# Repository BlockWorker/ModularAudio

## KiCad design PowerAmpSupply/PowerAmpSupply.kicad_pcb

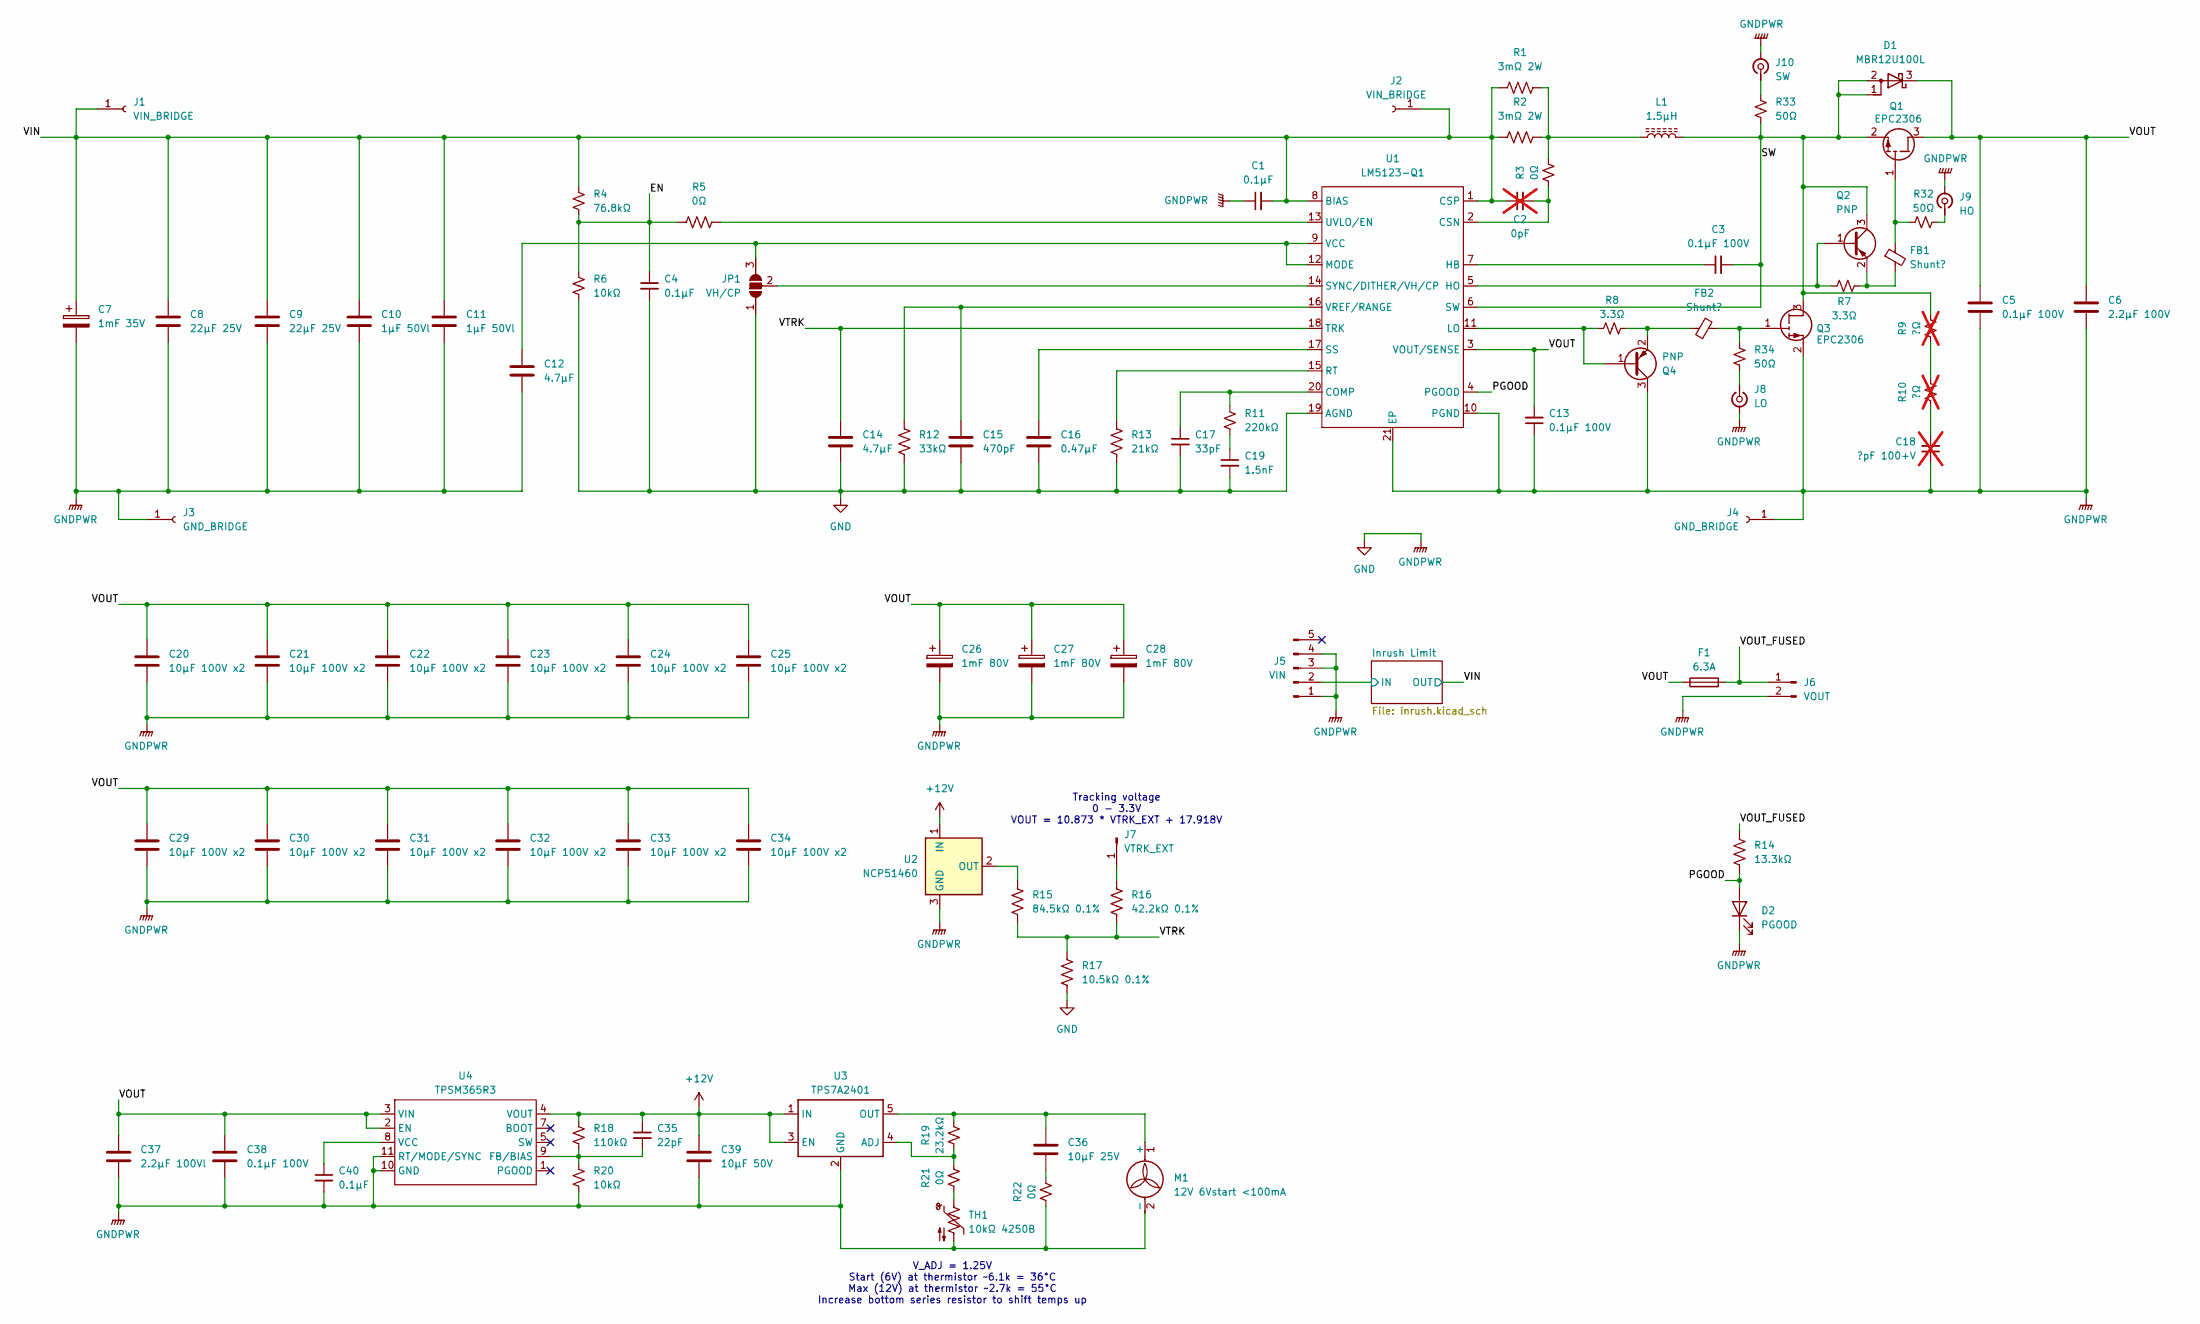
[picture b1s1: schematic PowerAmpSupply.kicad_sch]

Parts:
C1, C4, C40: 0.1µF; C_0603_1608Metric
C2: 0pF; C_0603_1608Metric; not fitted
C3, C5, C13, C38: 0.1µF 100V; C_0603_1608Metric
C6: 2.2µF 100V; C_0805_2012Metric
C7: 1mF 35V; CP_Radial_D10.0mm_P5.00mm
C8, C9: 22µF 25V; C_1210_3225Metric
C10, C11: 1µF 50Vl; C_0805_2012Metric
C12, C14: 4.7µF; C_0603_1608Metric
C15: 470pF; C_0603_1608Metric
C16: 0.47µF; C_0603_1608Metric
C17: 33pF; C_0603_1608Metric
C18: ?pF 100+V; C_0603_1608Metric; not fitted
C19: 1.5nF; C_0603_1608Metric
C20, C21, C22, C23, C24, C25, C29, C30, C31, C32, C33, C34: 10µF 100V x2; C_1210_3225Metric
C26, C27, C28: 1mF 80V; CP_Radial_D16.0mm_P7.50mm
C35: 22pF; C_0603_1608Metric
C36: 10µF 25V; C_0805_2012Metric
C37: 2.2µF 100Vl; C_1206_3216Metric
C39: 10µF 50V; C_1206_3216Metric
D1: MBR12U100L; TO-277B
D2: PGOOD; LED_0805_2012Metric
F1: 6.3A; Fuse_Schurter_MSB
FB1, FB2: Shunt?; L_0402_1005Metric_Pad0.77x0.64mm_HandSolder
J1, J2: VIN_BRIDGE; HolePad_2.5mm_3.5mm
J3, J4: GND_BRIDGE; HolePad_2.5mm_3.5mm
J5: VIN; TE_2042274_Solder
J6: VOUT; TE_644749-2
J7: VTRK_EXT; PinHeader_1x01_P2.54mm_Vertical
J8: LO; TE_CONMHF1-SMD
J9: HO; TE_CONMHF1-SMD
J10: SW; TE_CONMHF1-SMD
JP1: VH/CP; SolderJumper-3_P1.3mm_Open_RoundedPad1.0x1.5mm
L1: 1.5µH; L_Vishay_IHLP-6767
M1: 12V 6Vstart <100mA; Amphenol_MINITEK_0.8_2P_V_BoardEdge
Q1, Q3: EPC2306
Q2, Q4: PNP; HUSON-3-1EP_2x2mm_P1.3mm_EP1.1x1.6mm
R1, R2: 3mΩ 2W; R_0612_1632Metric
R3, R5, R21, R22: 0Ω; R_0603_1608Metric
R4: 76.8kΩ; R_0603_1608Metric
R6, R20: 10kΩ; R_0603_1608Metric
R7, R8: 3.3Ω; R_0603_1608Metric
R9, R10: ?Ω; R_1206_3216Metric; not fitted
R11: 220kΩ; R_0603_1608Metric
R12: 33kΩ; R_0603_1608Metric
R13: 21kΩ; R_0603_1608Metric
R14: 13.3kΩ; R_0603_1608Metric
R15: 84.5kΩ 0.1%; R_0603_1608Metric
R16: 42.2kΩ 0.1%; R_0603_1608Metric
R17: 10.5kΩ 0.1%; R_0603_1608Metric
R18: 110kΩ; R_0603_1608Metric
R19: 23.2kΩ; R_0603_1608Metric
R32, R33, R34: 50Ω; R_0402_1005Metric_Pad0.72x0.64mm_HandSolder
TH1: 10kΩ 4250B; R_0402_1005Metric_Pad0.72x0.64mm_HandSolder
U1: LM5123-Q1; VQFN-20-1EP_3.5x3.5mm_P0.5mm_EP2.05x2.05mm
U2: NCP51460; SOT-23
U3: TPS7A2401; SOT-23-5
U4: TPSM365R3; TI_QFN-FCMOD-HR

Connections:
+12V: C35.1, C39.1, R18.1, U2.1 (IN), U3.1 (IN), U3.3 (EN), U4.4 (VOUT)
/EN: C4.1, R4.2, R5.1, R6.1
/Inrush Limit/IN: J5.2; also elsewhere on the board
/PGOOD: D2.2 (A), R14.2, U1.4 (PGOOD)
/SW: C3.2, D1.1 (A), D1.2 (A), L1.2, Q1.2 (S), Q1.4 (S), Q1.6 (S), Q2.3 (C), Q3.3 (D), Q3.5 (D), Q3.7 (D), R9.2, R33.2, U1.6 (SW)
/VIN: C1.2, C2.1, C7.1, C8.1, C9.1, C10.1, C11.1, J1.1, J2.1, R1.1, R2.1, R4.1, U1.1 (CSP), U1.8 (BIAS); also elsewhere on the board
/VOUT: C5.1, C6.1, C13.2, C20.1, C21.1, C22.1, C23.1, C24.1, C25.1, C26.1, C27.1, C28.1, C29.1, C30.1, C31.1, C32.1, C33.1, C34.1, C37.1, C38.1, D1.3 (K), F1.1, Q1.3 (D), Q1.5 (D), Q1.7 (D), U1.3 (VOUT/SENSE), U4.2 (EN), U4.3 (VIN)
/VOUT_FUSED: F1.2, J6.1, R14.1
/VTRK: C14.1, R15.2, R16.2, R17.1, U1.18 (TRK)
GND: C1.1, C4.2, C5.2, C6.2, C7.2, C8.2, C9.2, C10.2, C11.2, C12.2, C13.1, C14.2, C15.2, C16.2, C17.2, C18.1, C19.2, C20.2, C21.2, C22.2, C23.2, C24.2, C25.2, C26.2, C27.2, C28.2, C29.2, C30.2, C31.2, C32.2, C33.2, C34.2, C37.2, C38.2, C39.2, C40.2, D2.1 (K), J3.1, J4.1, J5.1, J5.3, J5.4, J6.2, J8.2 (Ext), J9.2 (Ext), J10.2 (Ext), JP1.1 (A), M1.2 (-), Q3.2 (S), Q3.4 (S), Q3.6 (S), Q4.3 (C), R6.2, R12.2, R13.2, R17.2, R20.2, R22.2, TH1.2, U1.10 (PGND), U1.19 (AGND), U1.21 (EP), U2.3 (GND), U3.2 (GND), U4.10 (GND), U4.11 (RT/MODE/SYNC); also elsewhere on the board
unnamed: C18.2, R10.1
unnamed: C19.1, R11.2
unnamed: C36.2, R22.1
unnamed: J7.1, R16.1
unnamed: J8.1 (In), R34.2
unnamed: J9.1 (In), R32.2
unnamed: J10.1 (In), R33.1
unnamed: C12.1, JP1.3 (B), U1.9 (VCC), U1.12 (MODE)
unnamed: JP1.2 (C), U1.14 (SYNC/DITHER/VH/CP)
unnamed: L1.1, R1.2, R2.2, R3.2
unnamed: C36.1, M1.1 (+), R19.1, U3.5 (OUT)
unnamed: FB1.1, Q1.1 (G), R32.1
unnamed: Q2.1 (B), R7.1, U1.5 (HO)
unnamed: FB1.2, Q2.2 (E), R7.2
unnamed: FB2.2, Q3.1 (G), R34.1
unnamed: Q4.1 (B), R8.1, U1.11 (LO)
unnamed: FB2.1, Q4.2 (E), R8.2
unnamed: R9.1, R10.2
unnamed: R21.2, TH1.1
unnamed: C17.1, R11.1, U1.20 (COMP)
unnamed: C2.2, R3.1, U1.2 (CSN)
unnamed: C3.1, U1.7 (HB)
unnamed: R13.1, U1.15 (RT)
unnamed: C16.1, U1.17 (SS)
unnamed: R5.2, U1.13 (UVLO/EN)
unnamed: C15.1, R12.1, U1.16 (VREF/RANGE)
unnamed: R15.1, U2.2 (OUT)
unnamed: R19.2, R21.1, U3.4 (ADJ)
unnamed: C35.2, R18.2, R20.1, U4.9 (FB/BIAS)
unnamed: C40.1, U4.8 (VCC)

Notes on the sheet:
V_ADJ = 1.25V Start (6V) at thermistor ~6.1k = 36°C Max (12V) at thermistor ~2.7k = 55°C Increase bottom series resistor to shift temps up
Tracking voltage 0 - 3.3V VOUT = 10.873 * VTRK_EXT + 17.918V

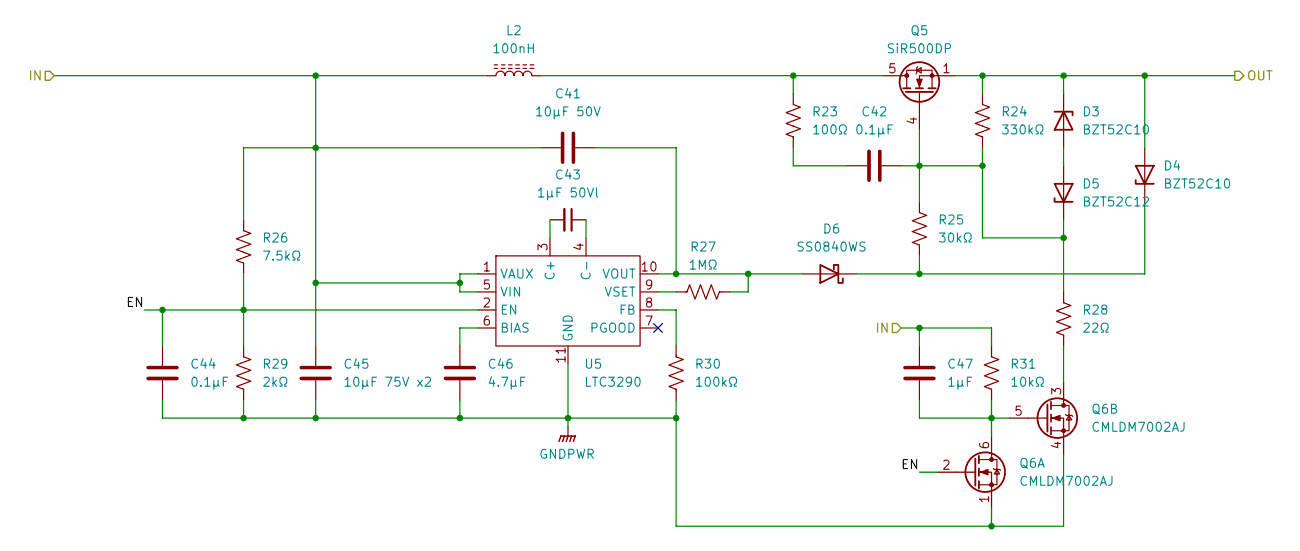
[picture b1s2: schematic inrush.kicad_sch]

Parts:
C41: 10µF 50V; C_1206_3216Metric
C42, C44: 0.1µF; C_0603_1608Metric
C43: 1µF 50Vl; C_0805_2012Metric
C45: 10µF 75V x2; C_1210_3225Metric
C46: 4.7µF; C_0603_1608Metric
C47: 1µF; C_0603_1608Metric
D3, D4: BZT52C10; D_SOD-123
D5: BZT52C12; D_SOD-123
D6: SS0840WS; D_SOD-323_HandSoldering
L2: 100nH; L_Pulse_PG2110HLT
Q5: SiR500DP; PowerPAK_SO-8_Single
Q6: CMLDM7002AJ; SOT-563
R23: 100Ω; R_0603_1608Metric
R24: 330kΩ; R_0603_1608Metric
R25: 30kΩ; R_0603_1608Metric
R26: 7.5kΩ; R_0603_1608Metric
R27: 1MΩ; R_0603_1608Metric
R28: 22Ω; R_0603_1608Metric
R29: 2kΩ; R_0603_1608Metric
R30: 100kΩ; R_0603_1608Metric
R31: 10kΩ; R_0603_1608Metric
U5: LTC3290; MSOP-10-1EP_3x3mm_P0.5mm_EP1.68x1.88mm

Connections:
/Inrush Limit/EN: C44.1, Q6.2 (G), R26.2, R29.1, U5.2 (EN)
/Inrush Limit/IN: C41.1, C45.1, C47.1, L2.1, R26.1, R31.1, U5.1 (VAUX), U5.5 (VIN); also elsewhere on the board
/VIN: D3.1 (K), D4.2 (A), Q5.1 (S), Q5.2 (S), Q5.3 (S), R24.1; also elsewhere on the board
GND: C44.2, C45.2, C46.2, Q6.1 (S), Q6.4 (S), R29.2, R30.2, U5.11 (GND); also elsewhere on the board
unnamed: C42.1, R23.2
unnamed: D3.2 (A), D5.2 (A)
unnamed: D4.1 (K), D6.1 (K), R25.2
unnamed: C42.2, D5.1 (K), Q5.4 (G), R24.2, R25.1, R28.1
unnamed: C41.2, D6.2 (A), R27.2, U5.10 (VOUT)
unnamed: L2.2, Q5.5 (D), R23.1
unnamed: C47.2, Q6.5 (G), Q6.6 (D), R31.2
unnamed: Q6.3 (D), R28.2
unnamed: C46.1, U5.6 (BIAS)
unnamed: C43.2, U5.3 (C+)
unnamed: C43.1, U5.4 (C-)
unnamed: R30.1, U5.8 (FB)
unnamed: R27.1, U5.9 (VSET)

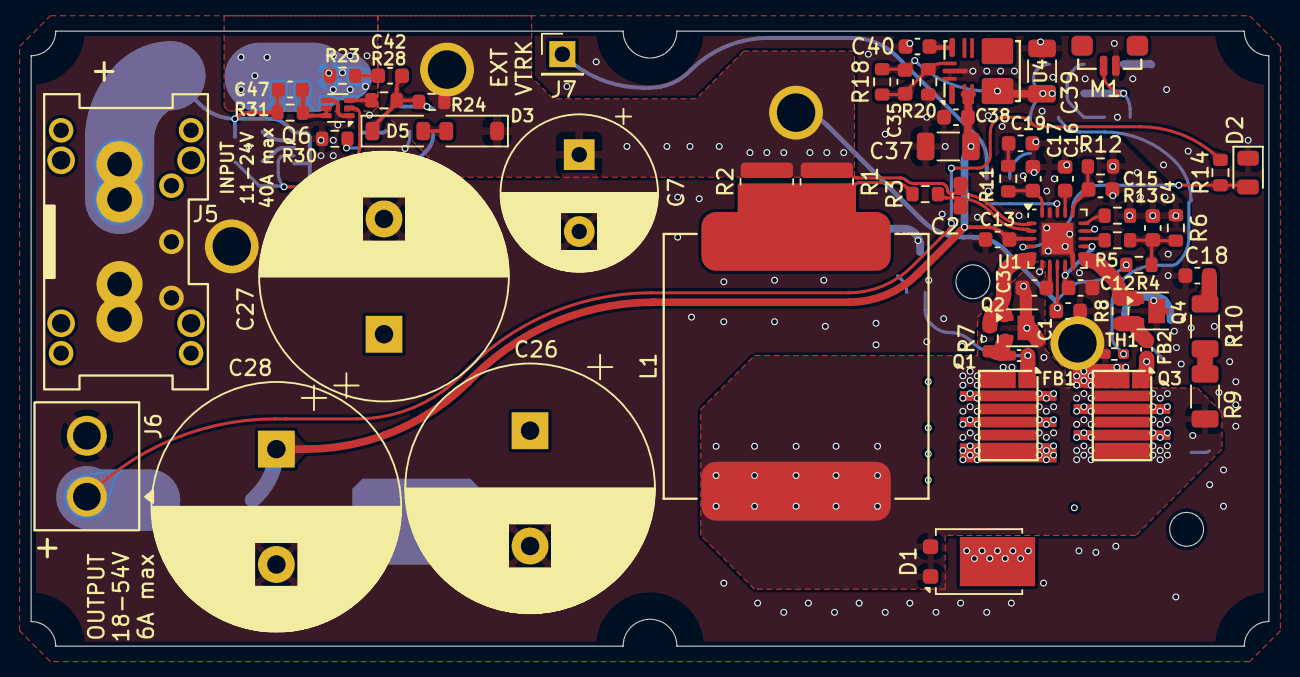
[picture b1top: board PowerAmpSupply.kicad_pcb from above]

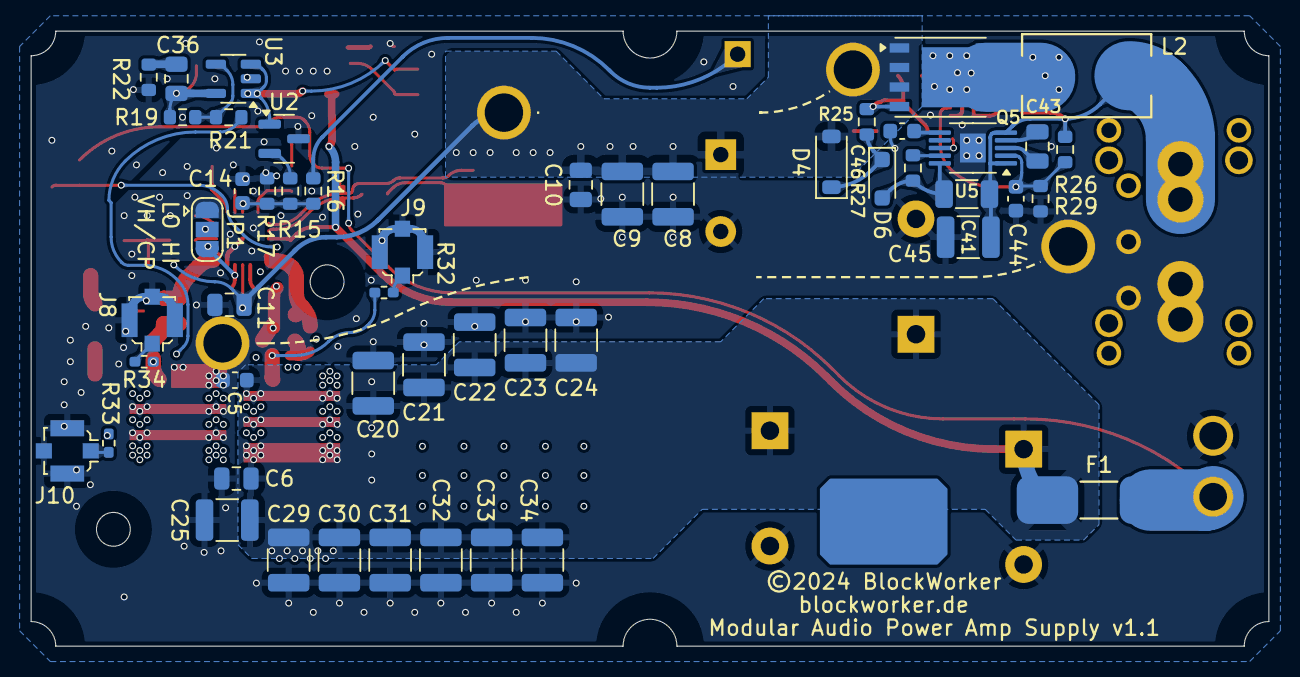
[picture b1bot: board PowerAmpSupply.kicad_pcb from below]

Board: 4 copper layers, 80.5 x 40.0 mm, 118 parts (51 on the bottom side), 54 nets.

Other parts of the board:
HS: ATS-xPX035035035_NoMounts
Logo: BW_Logo_7.5x4.8mm

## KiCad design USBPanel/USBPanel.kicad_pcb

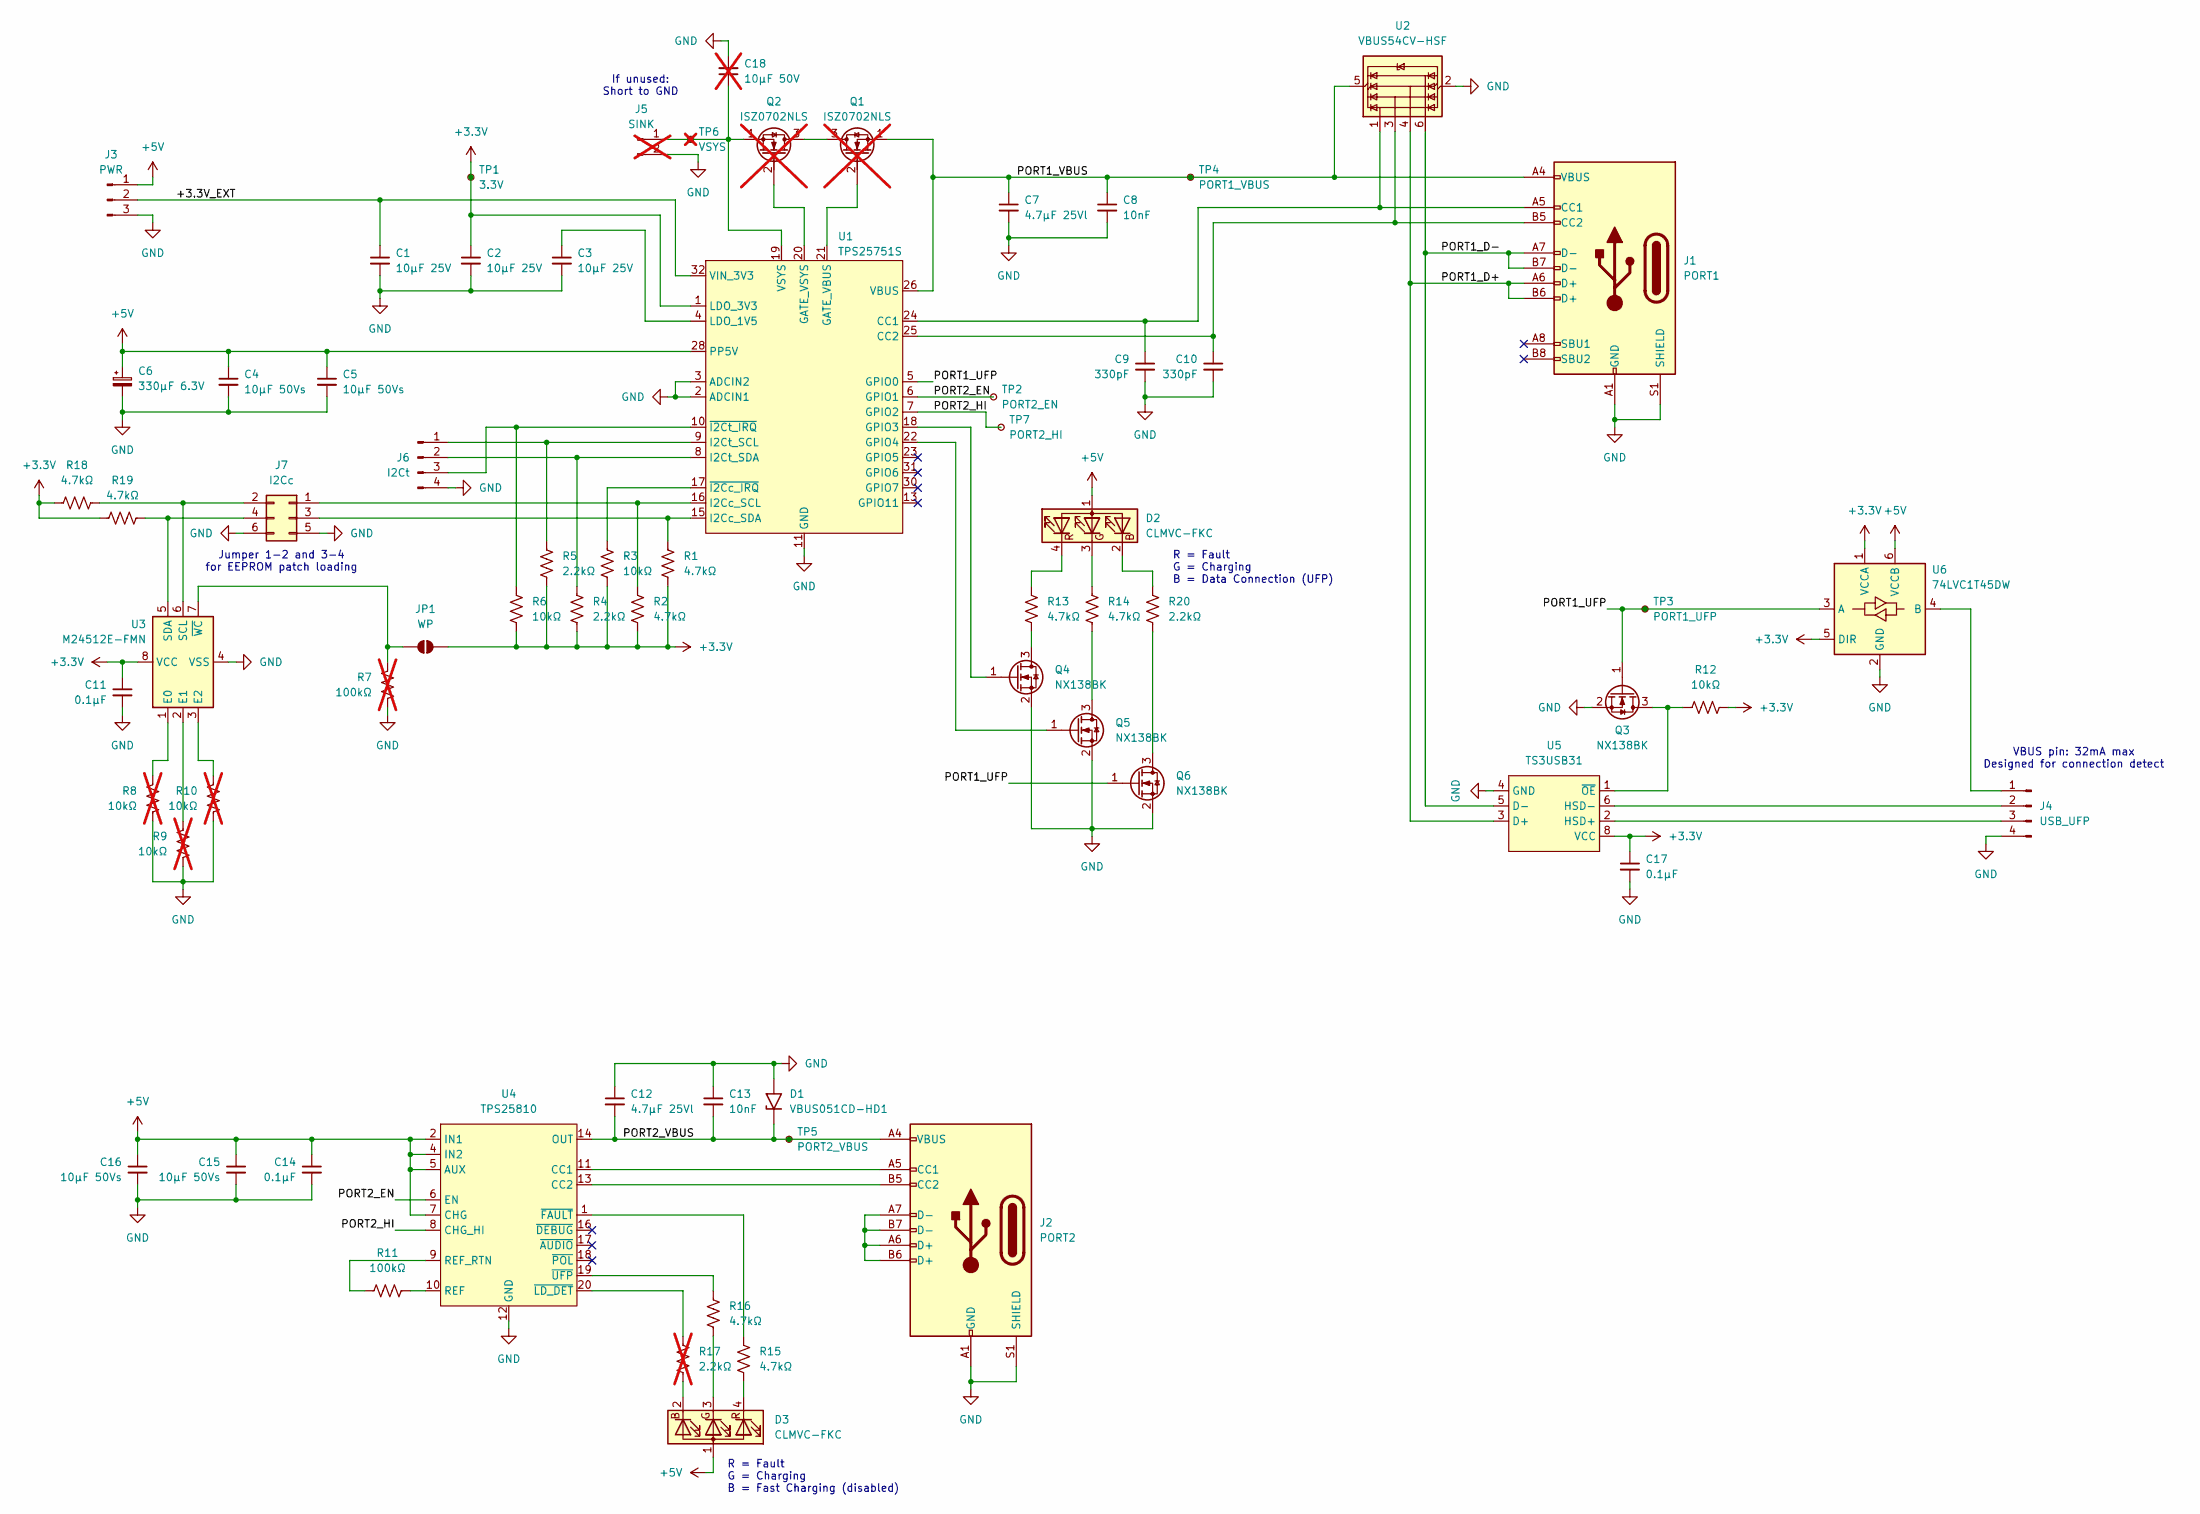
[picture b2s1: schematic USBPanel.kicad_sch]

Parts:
C1, C2, C3: 10μF 25V; C_0805_2012Metric
C4, C5, C15, C16: 10μF 50Vs; C_0805_2012Metric
C6: 330μF 6.3V; CP_Elec_6.3x5.9
C7, C12: 4.7μF 25Vl; C_0805_2012Metric
C8, C13: 10nF; C_0603_1608Metric
C9, C10: 330pF; C_0603_1608Metric
C11, C14, C17: 0.1μF; C_0603_1608Metric
C18: 10μF 50V; C_1206_3216Metric; not fitted
D1: VBUS051CD-HD1; D_0402_1005Metric
D2, D3: CLMVC-FKC; LED_Cree-PLCC4_2x2mm_CW
J1: PORT1; USB_C_Receptacle_Amphenol_12402082E512A
J2: PORT2; USB_C_Receptacle_Amphenol_12402082E512A
J3: PWR; Molex_Nano-Fit_105309-xx03_1x03_P2.50mm_Vertical
J4: USB_UFP; Amphenol_MINITEK_WTB_1.25_4P
J5: SINK; Molex_Nano-Fit_105309-xx02_1x02_P2.50mm_Vertical; not fitted
J6: I2Ct; PinHeader_1x04_P2.54mm_Vertical
J7: I2Cc; PinHeader_2x03_P2.54mm_Vertical
JP1: WP; SolderJumper-2_P1.3mm_Open_RoundedPad1.0x1.5mm
Q1, Q2: ISZ0702NLS; Infineon_PG-TSDSON-8-40; not fitted
Q3, Q4, Q5, Q6: NX138BK; SOT-23
R1, R2, R13, R14, R15, R16, R18, R19: 4.7kΩ; R_0603_1608Metric
R3, R6, R12: 10kΩ; R_0603_1608Metric
R4, R5, R20: 2.2kΩ; R_0603_1608Metric
R7: 100kΩ; R_0603_1608Metric; not fitted
R8, R9, R10: 10kΩ; R_0603_1608Metric; not fitted
R11: 100kΩ; R_0603_1608Metric
R17: 2.2kΩ; R_0603_1608Metric; not fitted
TP1: 3.3V; TP_0603_1608Metric_Fused
TP2: PORT2_EN; TP_0603_1608Metric_Fused
TP3: PORT1_UFP; TP_0603_1608Metric_Fused
TP4: PORT1_VBUS; TP_0603_1608Metric_Fused
TP5: PORT2_VBUS; TP_0603_1608Metric_Fused
TP6: VSYS; TP_0603_1608Metric_Fused; not fitted
TP7: PORT2_HI; TP_0603_1608Metric_Fused
U1: TPS25751S; VQFN-32-1EP_4x4mm_P0.4mm_EP2.8x2.8mm
U2: VBUS54CV-HSF; Vishay_LLP75-6L
U3: M24512E-FMN; SOIC-8_3.9x4.9mm_P1.27mm
U4: TPS25810; Texas_RVC0020A_WQFN-20-1EP_3x4mm_P0.5mm_EP2.6x1.6mm
U5: TS3USB31; Texas_RSE0008A_UQFN-8_1.5x1.5mm_P0.5mm
U6: 74LVC1T45DW; SOT-363_SC-70-6

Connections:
+3.3V: C2.1, C11.1, C17.1, JP1.2 (B), R1.2, R2.2, R3.2, R4.2, R5.2, R6.2, R12.1, R18.1, R19.1, TP1.1, U1.1 (LDO_3V3), U3.8 (VCC), U5.8 (VCC), U6.1 (VCCA), U6.5 (DIR)
+5V: C4.1, C5.1, C6.1, C14.1, C15.1, C16.1, D2.1 (A), D3.1 (A), J3.1, U1.28 (PP5V), U1.29 (PP5V), U4.2 (IN1), U4.3 (IN1), U4.4 (IN2), U4.5 (AUX), U4.7 (CHG), U6.6 (VCCB)
/+3.3V_EXT: C1.1, J3.2, U1.32 (VIN_3V3)
/PORT1_D+: J1.A6 (D+), J1.B6 (D+), U2.4 (I/O3), U5.3 (D+)
/PORT1_D-: J1.A7 (D-), J1.B7 (D-), U2.6 (I/O4), U5.5 (D-)
/PORT1_UFP: Q3.1 (G), Q6.1 (G), TP3.1, U1.5 (GPIO0), U6.3 (A)
/PORT1_VBUS: C7.1, C8.1, J1.A4 (VBUS), J1.A9 (VBUS), J1.B4 (VBUS), J1.B9 (VBUS), Q1.1 (S), TP4.1, U1.26 (VBUS), U1.27 (VBUS), U2.5 (VBUS)
/PORT2_EN: TP2.1, U1.6 (GPIO1), U4.6 (EN)
/PORT2_HI: TP7.1, U1.7 (GPIO2), U4.8 (CHG_HI)
/PORT2_VBUS: C12.2, C13.2, D1.1 (A1), J2.A4 (VBUS), J2.A9 (VBUS), J2.B4 (VBUS), J2.B9 (VBUS), TP5.1, U4.14 (OUT), U4.15 (OUT)
GND: C1.2, C2.2, C3.2, C4.2, C5.2, C6.2, C7.2, C8.2, C9.2, C10.2, C11.2, C12.1, C13.1, C14.2, C15.2, C16.2, C17.2, C18.2, D1.2 (A2), J1.A1 (GND), J1.A12 (GND), J1.B1 (GND), J1.B12 (GND), J1.S1 (SHIELD), J2.A1 (GND), J2.A12 (GND), J2.B1 (GND), J2.B12 (GND), J2.S1 (SHIELD), J3.3, J4.4, J5.2, J6.4, J7.5, J7.6, Q3.2 (S), Q4.2 (S), Q5.2 (S), Q6.2 (S), R7.2, R8.2, R9.2, R10.2, U1.2 (ADCIN1), U1.3 (ADCIN2), U1.11 (GND), U1.12 (GND), U1.14 (GND), U1.33 (GND), U2.2 (GND), U3.4 (VSS), U4.12 (GND), U4.21 (GND), U5.4 (GND), U6.2 (GND)
unnamed: D2.2 (BK), R20.1
unnamed: D2.3 (GK), R14.1
unnamed: D2.4 (RK), R13.1
unnamed: D3.2 (BK), R17.2
unnamed: D3.3 (GK), R16.2
unnamed: D3.4 (RK), R15.2
unnamed: C9.1, J1.A5 (CC1), U1.24 (CC1), U2.1 (I/O1)
unnamed: C10.1, J1.B5 (CC2), U1.25 (CC2), U2.3 (I/O2)
unnamed: J2.A5 (CC1), U4.11 (CC1)
unnamed: J2.B5 (CC2), U4.13 (CC2)
unnamed: J2.A6 (D+), J2.A7 (D-), J2.B6 (D+), J2.B7 (D-)
unnamed: J4.1, U6.4 (B)
unnamed: J4.2, U5.6 (HSD-)
unnamed: J4.3, U5.2 (HSD+)
unnamed: C18.1, J5.1, Q2.1 (S), TP6.1, U1.19 (VSYS)
unnamed: J6.1, R5.1, U1.9 (I2Ct_SCL)
unnamed: J6.2, R4.1, U1.8 (I2Ct_SDA)
unnamed: J6.3, R6.1, U1.10 (~I2Ct_IRQ)
unnamed: J7.1, R2.1, U1.16 (I2Cc_SCL)
unnamed: J7.2, R18.2, U3.6 (SCL)
unnamed: J7.3, R1.1, U1.15 (I2Cc_SDA)
unnamed: J7.4, R19.2, U3.5 (SDA)
unnamed: JP1.1 (A), R7.1, U3.7 (~WC)
unnamed: Q1.3 (D), Q2.3 (D)
unnamed: Q1.2 (G), U1.21 (GATE_VBUS)
unnamed: Q2.2 (G), U1.20 (GATE_VSYS)
unnamed: Q3.3 (D), R12.2, U5.1 (~OE)
unnamed: Q4.3 (D), R13.2
unnamed: Q4.1 (G), U1.18 (GPIO3)
unnamed: Q5.3 (D), R14.2
unnamed: Q5.1 (G), U1.22 (GPIO4)
unnamed: Q6.3 (D), R20.2
unnamed: C3.1, U1.4 (LDO_1V5)
unnamed: R3.1, U1.17 (~I2Cc_IRQ)
unnamed: R8.1, U3.1 (E0)
unnamed: R9.1, U3.2 (E1)
unnamed: R10.1, U3.3 (E2)
unnamed: R11.2, U4.10 (REF)
unnamed: R11.1, U4.9 (REF_RTN)
unnamed: R15.1, U4.1 (~FAULT)
unnamed: R17.1, U4.20 (~LD_DET)
unnamed: R16.1, U4.19 (~UFP)

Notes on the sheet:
Jumper 1-2 and 3-4 for EEPROM patch loading
VBUS pin: 32mA max Designed for connection detect
R = Fault G = Charging B = Fast Charging (disabled)
R = Fault G = Charging B = Data Connection (UFP)
If unused: Short to GND

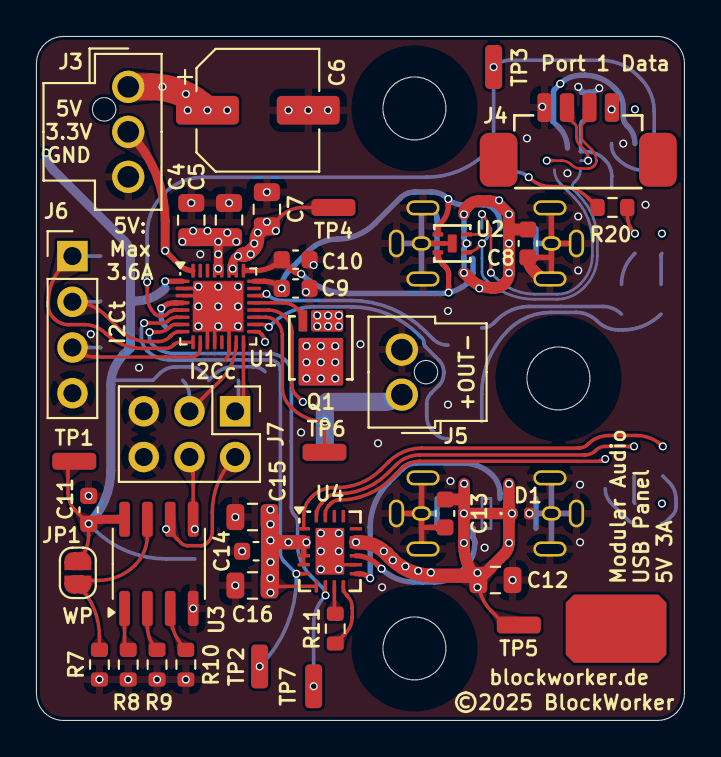
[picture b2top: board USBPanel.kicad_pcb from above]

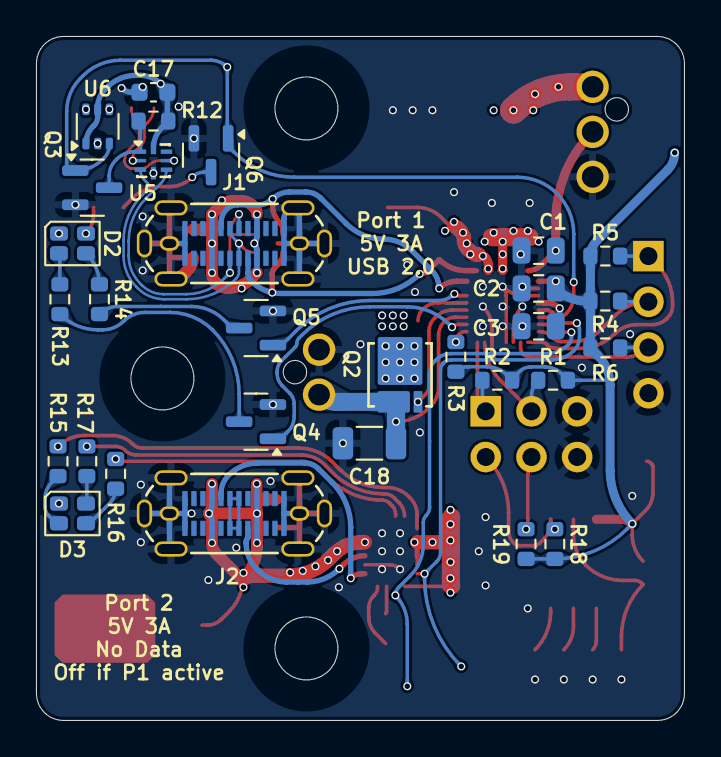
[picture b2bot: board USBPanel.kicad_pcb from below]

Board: 6 copper layers, 36.0 x 38.0 mm, 68 parts (30 on the bottom side), 53 nets.

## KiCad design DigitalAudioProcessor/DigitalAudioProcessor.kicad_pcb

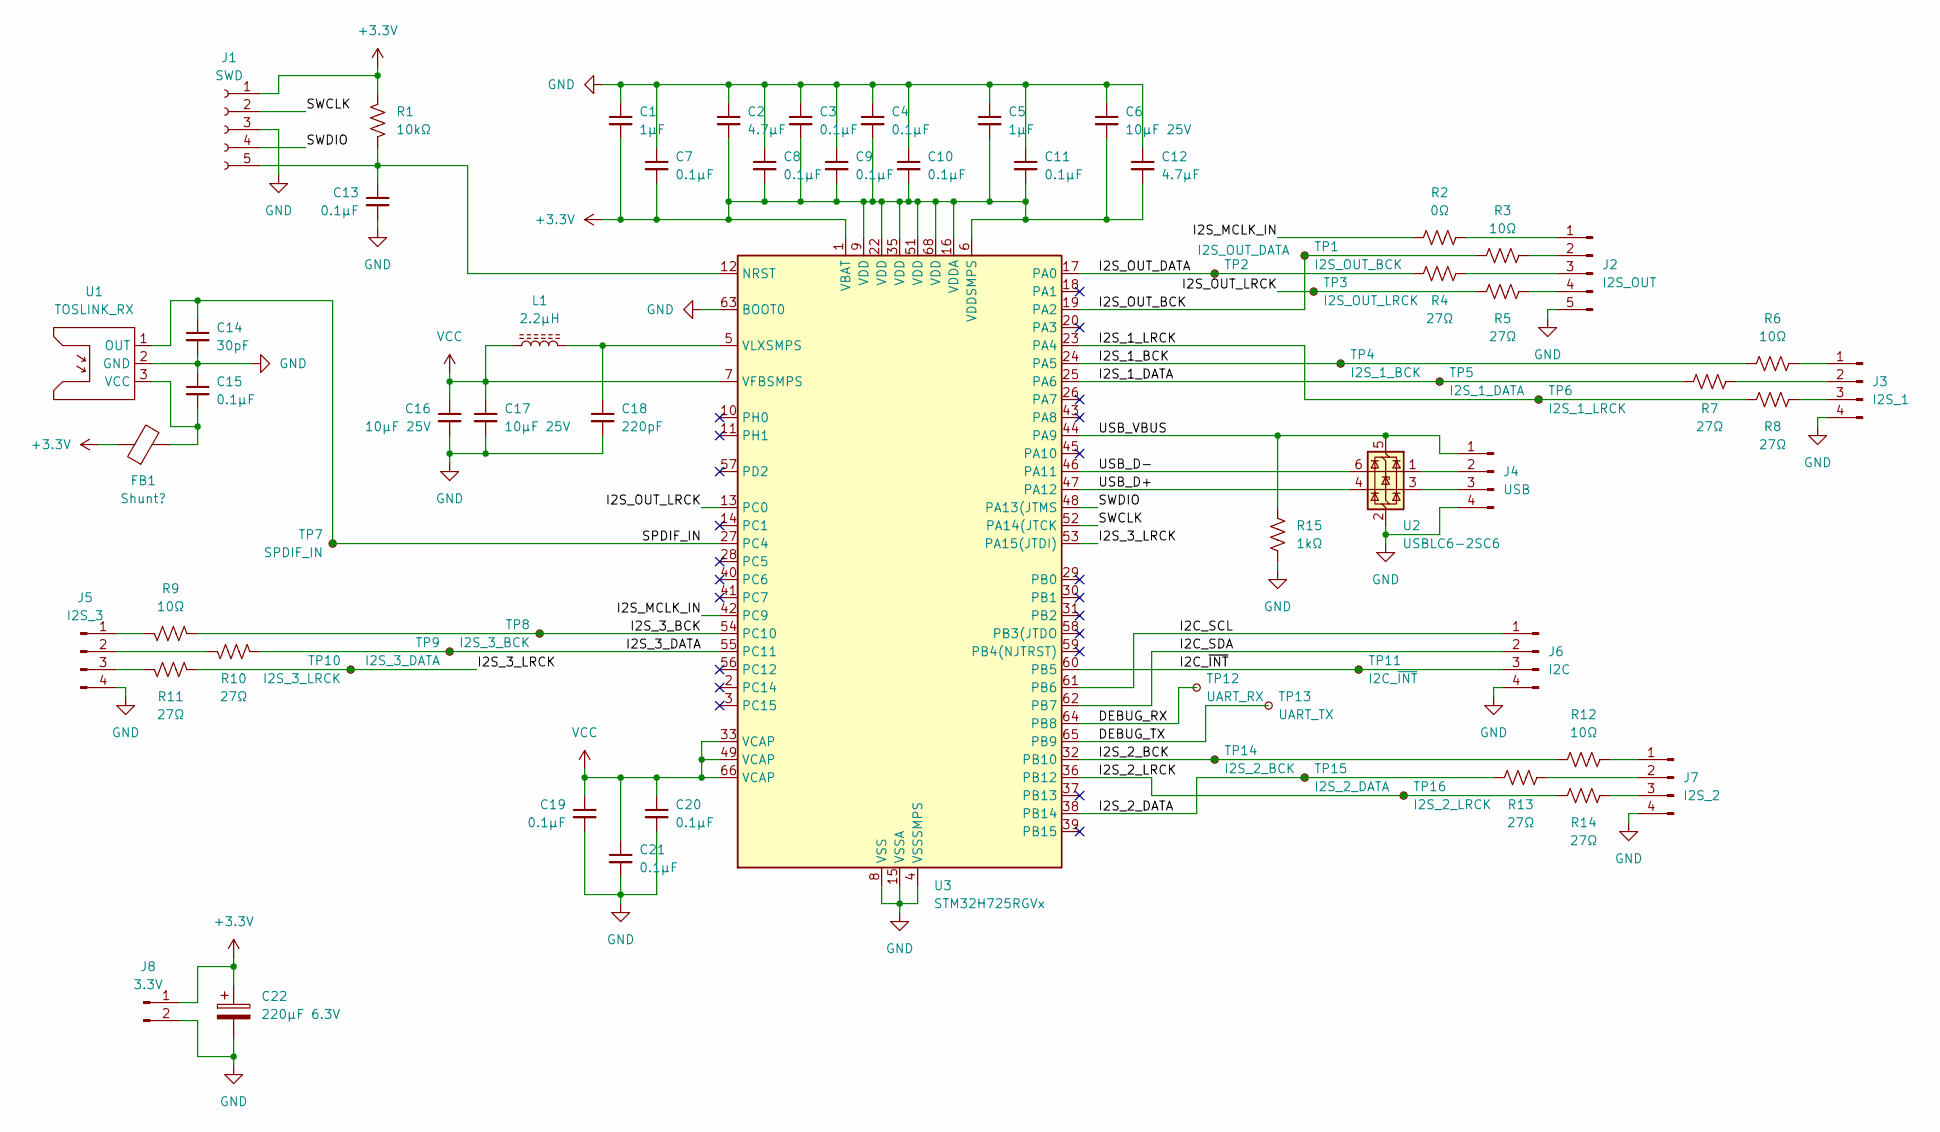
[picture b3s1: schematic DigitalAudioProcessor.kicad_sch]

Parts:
C1, C5: 1µF; C_0603_1608Metric
C2, C12: 4.7µF; C_0603_1608Metric
C3, C4, C7, C8, C9, C10, C11, C13, C15, C19, C20, C21: 0.1µF; C_0603_1608Metric
C6, C16, C17: 10µF 25V; C_0805_2012Metric
C14: 30pF; C_0603_1608Metric
C18: 220pF; C_0603_1608Metric
C22: 220µF 6.3V; CP_Elec_5x5.8
FB1: Shunt?; L_0603_1608Metric
J1: SWD; PinSocket_1x05_P1.27mm_Vertical_SMD_Pin1Right
J2: I2S_OUT; Amphenol_MINITEK_WTB_1.25_5P
J3: I2S_1; Amphenol_MINITEK_WTB_1.25_4P
J4: USB; Amphenol_MINITEK_WTB_1.25_4P
J5: I2S_3; Amphenol_MINITEK_WTB_1.25_4P
J6: I2C; Amphenol_MINITEK_WTB_1.25_4P
J7: I2S_2; Amphenol_MINITEK_WTB_1.25_4P
J8: 3.3V; Amphenol_MINITEK_WTB_1.25_2P
L1: 2.2µH; L_0805_2012Metric
R1: 10kΩ; R_0603_1608Metric
R2: 0Ω; R_0603_1608Metric
R3, R6, R9, R12: 10Ω; R_0603_1608Metric
R4, R5, R7, R8, R10, R11, R13, R14: 27Ω; R_0603_1608Metric
R15: 1kΩ; R_0603_1608Metric
TP1: I2S_OUT_BCK; TP_0603_1608Metric_Fused
TP2: I2S_OUT_DATA; TP_0603_1608Metric_Fused
TP3: I2S_OUT_LRCK; TP_0603_1608Metric_Fused
TP4: I2S_1_BCK; TP_0603_1608Metric_Fused
TP5: I2S_1_DATA; TP_0603_1608Metric_Fused
TP6: I2S_1_LRCK; TP_0603_1608Metric_Fused
TP7: SPDIF_IN; TP_0603_1608Metric_Fused
TP8: I2S_3_BCK; TP_0603_1608Metric_Fused
TP9: I2S_3_DATA; TP_0603_1608Metric_Fused
TP10: I2S_3_LRCK; TP_0603_1608Metric_Fused
TP11: I2C_~{INT}; TP_0603_1608Metric_Fused
TP12: UART_RX; TP_0603_1608Metric_Fused
TP13: UART_TX; TP_0603_1608Metric_Fused
TP14: I2S_2_BCK; TP_0603_1608Metric_Fused
TP15: I2S_2_DATA; TP_0603_1608Metric_Fused
TP16: I2S_2_LRCK; TP_0603_1608Metric_Fused
U1: TOSLINK_RX; DLR2180
U2: USBLC6-2SC6; SOT-23-6
U3: STM32H725RGVx; QFN-68-1EP_8x8mm_P0.4mm_EP6.4x6.4mm

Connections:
+3.3V: C1.2, C2.2, C3.2, C4.2, C5.2, C6.2, C7.2, C8.2, C9.2, C10.2, C11.2, C12.2, C22.1, FB1.1, J1.1, J8.1, R1.1, U3.1 (VBAT), U3.6 (VDDSMPS), U3.9 (VDD), U3.16 (VDDA), U3.22 (VDD), U3.35 (VDD), U3.51 (VDD), U3.68 (VDD)
/DEBUG_RX: TP12.1, U3.64 (PB8)
/DEBUG_TX: TP13.1, U3.65 (PB9)
/I2C_SCL: J6.1, U3.61 (PB6)
/I2C_SDA: J6.2, U3.62 (PB7)
/I2C_~INT: J6.3, TP11.1, U3.60 (PB5)
/I2S_1_BCK: R6.1, TP4.1, U3.24 (PA5)
/I2S_1_DATA: R7.1, TP5.1, U3.25 (PA6)
/I2S_1_LRCK: R8.1, TP6.1, U3.23 (PA4)
/I2S_2_BCK: R12.1, TP14.1, U3.32 (PB10)
/I2S_2_DATA: R13.1, TP15.1, U3.38 (PB14)
/I2S_2_LRCK: R14.1, TP16.1, U3.36 (PB12)
/I2S_3_BCK: R9.1, TP8.1, U3.54 (PC10)
/I2S_3_DATA: R10.1, TP9.1, U3.55 (PC11)
/I2S_3_LRCK: R11.1, TP10.1, U3.53 (PA15(JTDI))
/I2S_MCLK_IN: R2.1, U3.42 (PC9)
/I2S_OUT_BCK: R3.1, TP1.1, U3.19 (PA2)
/I2S_OUT_DATA: R4.1, TP2.1, U3.17 (PA0)
/I2S_OUT_LRCK: R5.1, TP3.1, U3.13 (PC0)
/SPDIF_IN: C14.1, TP7.1, U1.1 (OUT), U3.27 (PC4)
/SWCLK: J1.2, U3.52 (PA14(JTCK)
/SWDIO: J1.4, U3.48 (PA13(JTMS)
/USB_D+: U2.4 (I/O2), U3.47 (PA12)
/USB_D-: U2.6 (I/O1), U3.46 (PA11)
/USB_VBUS: J4.1, R15.2, U2.5 (VBUS), U3.44 (PA9)
GND: C1.1, C2.1, C3.1, C4.1, C5.1, C6.1, C7.1, C8.1, C9.1, C10.1, C11.1, C12.1, C13.2, C14.2, C15.1, C16.2, C17.2, C18.2, C19.2, C20.2, C21.2, C22.2, J1.3, J2.5, J3.4, J4.4, J5.4, J6.4, J7.4, J8.2, R15.1, U1.2 (GND), U2.2 (GND), U3.4 (VSSSMPS), U3.8 (VSS), U3.15 (VSSA), U3.21 (VSS), U3.34 (VSS), U3.50 (VSS), U3.63 (BOOT0), U3.67 (VSS), U3.69 (VSS)
unnamed: C13.1, J1.5, R1.2, U3.12 (NRST)
unnamed: J2.1, R2.2
unnamed: J2.2, R3.2
unnamed: J2.3, R4.2
unnamed: J2.4, R5.2
unnamed: J3.1, R6.2
unnamed: J3.2, R7.2
unnamed: J3.3, R8.2
unnamed: J4.2, U2.1 (I/O1)
unnamed: J4.3, U2.3 (I/O2)
unnamed: J5.1, R9.2
unnamed: J5.2, R10.2
unnamed: J5.3, R11.2
unnamed: J7.1, R12.2
unnamed: J7.2, R13.2
unnamed: J7.3, R14.2
unnamed: C15.2, FB1.2, U1.3 (VCC)
unnamed: C18.1, L1.2, U3.5 (VLXSMPS)
VCC: C16.1, C17.1, C19.1, C20.1, C21.1, L1.1, U3.7 (VFBSMPS), U3.33 (VCAP), U3.49 (VCAP), U3.66 (VCAP)

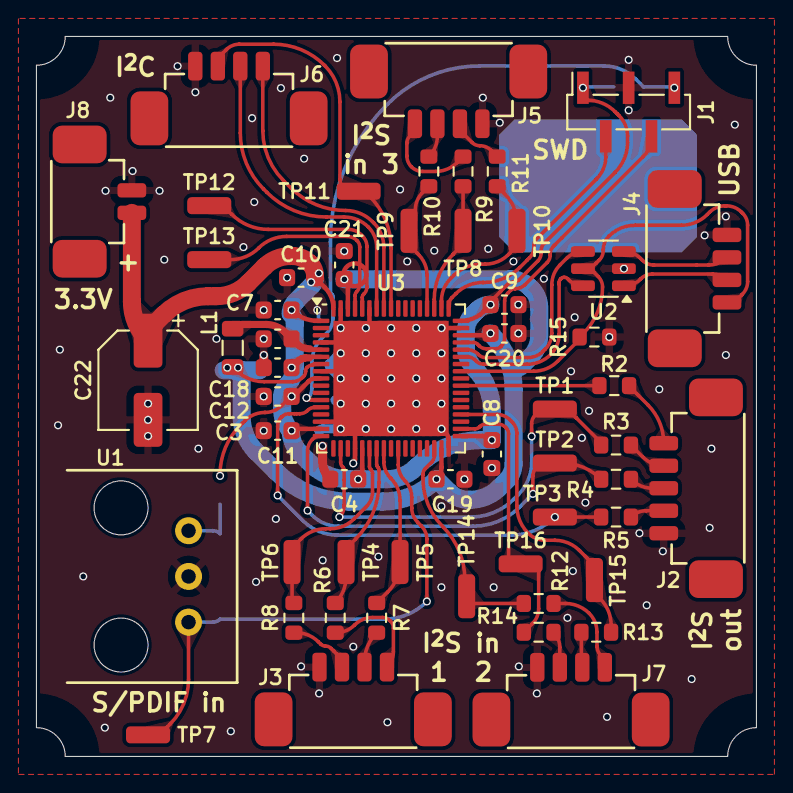
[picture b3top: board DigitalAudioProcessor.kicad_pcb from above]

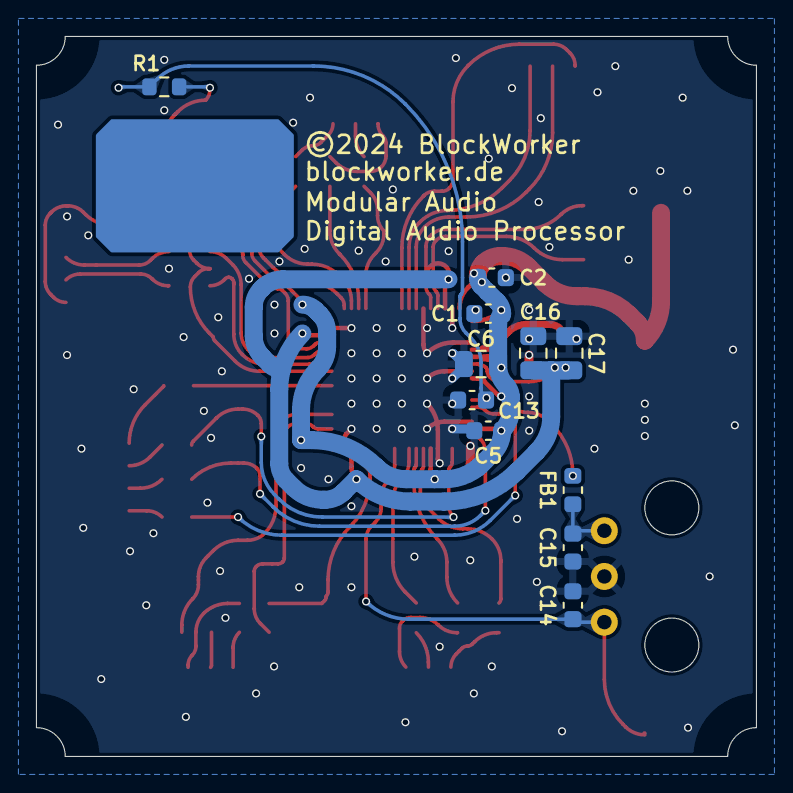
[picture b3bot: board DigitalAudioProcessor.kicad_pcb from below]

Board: 4 copper layers, 40.0 x 40.0 mm, 66 parts (11 on the bottom side), 45 nets.

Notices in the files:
parts and their libraries:
©2024 BlockWorker
©2025 BlockWorker
